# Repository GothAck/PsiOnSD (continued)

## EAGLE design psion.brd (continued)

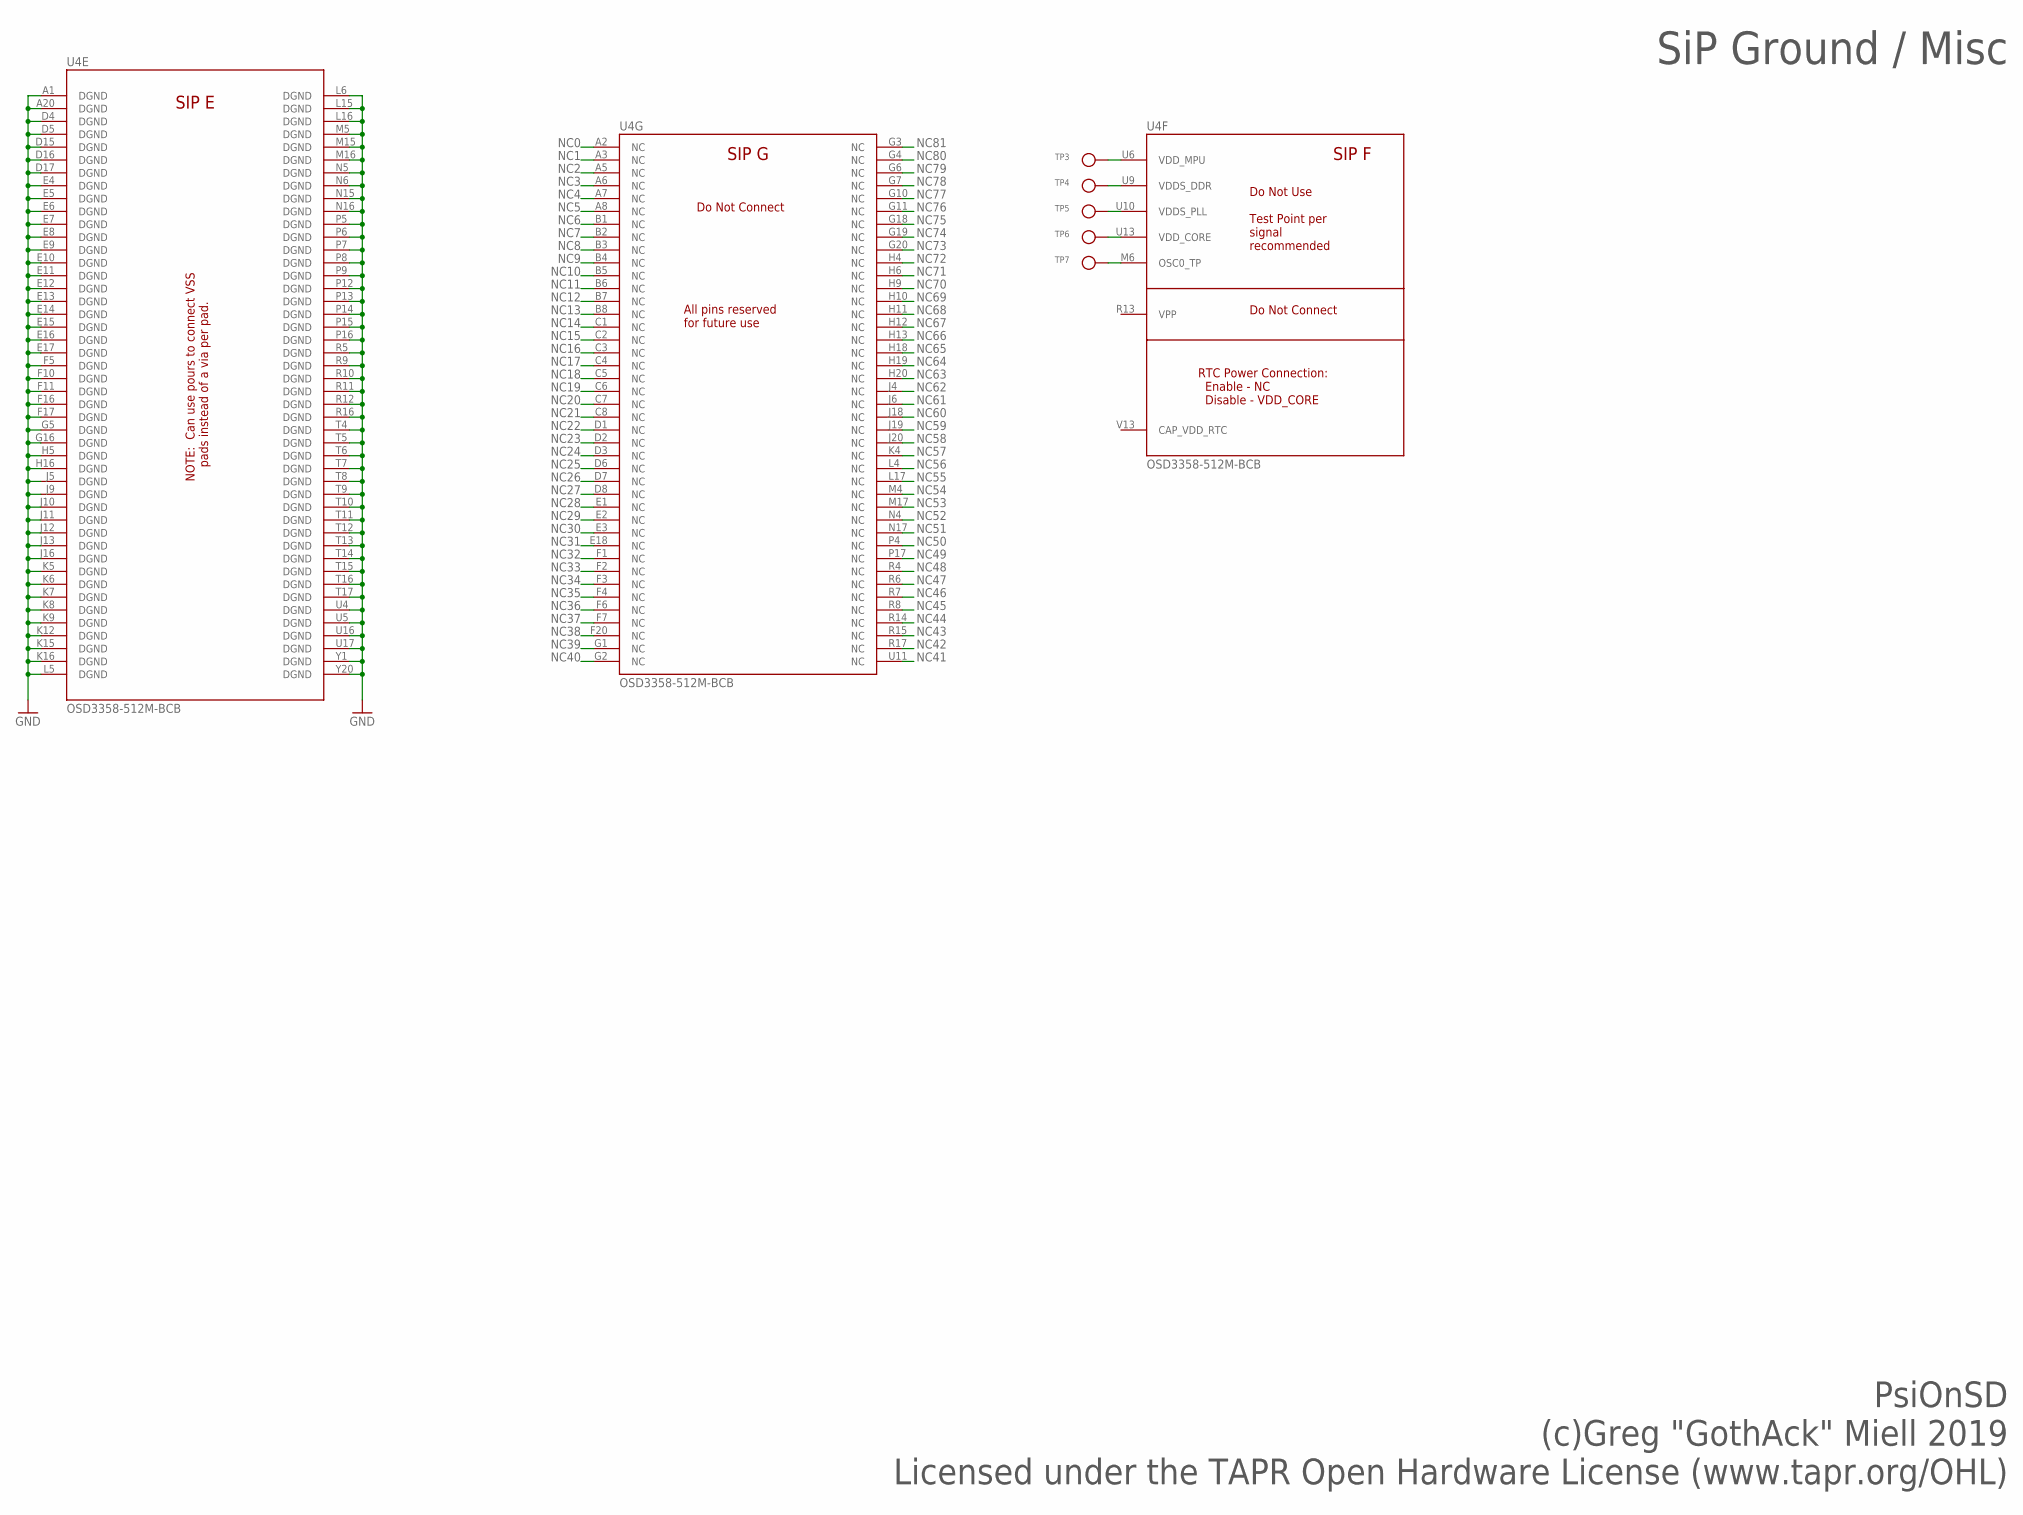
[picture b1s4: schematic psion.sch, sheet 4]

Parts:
TP3, TP4, TP5, TP6, TP7: TESTPOINTROUND1MM; TESTPOINT_ROUND_1MM
U4: OSD3358-512M-BCB; OSD335X-BGA-400

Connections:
GND: U4.A1 (DGND), U4.A20 (DGND), U4.D4 (DGND), U4.D5 (DGND), U4.D15 (DGND), U4.D16 (DGND), U4.D17 (DGND), U4.E4 (DGND), U4.E5 (DGND), U4.E6 (DGND), U4.E7 (DGND), U4.E8 (DGND), U4.E9 (DGND), U4.E10 (DGND), U4.E11 (DGND), U4.E12 (DGND), U4.E13 (DGND), U4.E14 (DGND), U4.E15 (DGND), U4.E16 (DGND), U4.E17 (DGND), U4.F5 (DGND), U4.F10 (DGND), U4.F11 (DGND), U4.F16 (DGND), U4.F17 (DGND), U4.G5 (DGND), U4.G16 (DGND), U4.H5 (DGND), U4.H16 (DGND), U4.J5 (DGND), U4.J9 (DGND), U4.J10 (DGND), U4.J11 (DGND), U4.J12 (DGND), U4.J13 (DGND), U4.J16 (DGND), U4.K5 (DGND), U4.K6 (DGND), U4.K7 (DGND), U4.K8 (DGND), U4.K9 (DGND), U4.K12 (DGND), U4.K15 (DGND), U4.K16 (DGND), U4.L5 (DGND), U4.L6 (DGND), U4.L15 (DGND), U4.L16 (DGND), U4.M5 (DGND), U4.M15 (DGND), U4.M16 (DGND), U4.N5 (DGND), U4.N6 (DGND), U4.N15 (DGND), U4.N16 (DGND), U4.P5 (DGND), U4.P6 (DGND), U4.P7 (DGND), U4.P8 (DGND), U4.P9 (DGND), U4.P12 (DGND), U4.P13 (DGND), U4.P14 (DGND), U4.P15 (DGND), U4.P16 (DGND), U4.R5 (DGND), U4.R9 (DGND), U4.R10 (DGND), U4.R11 (DGND), U4.R12 (DGND), U4.R16 (DGND), U4.T4 (DGND), U4.T5 (DGND), U4.T6 (DGND), U4.T7 (DGND), U4.T8 (DGND), U4.T9 (DGND), U4.T10 (DGND), U4.T11 (DGND), U4.T12 (DGND), U4.T13 (DGND), U4.T14 (DGND), U4.T15 (DGND), U4.T16 (DGND), U4.T17 (DGND), U4.U4 (DGND), U4.U5 (DGND), U4.U16 (DGND), U4.U17 (DGND), U4.Y1 (DGND), U4.Y20 (DGND); also elsewhere on the board
unnamed: TP3.P$1, U4.U6 (VDD_MPU)
unnamed: TP4.P$1, U4.U9 (VDDS_DDR)
unnamed: TP5.P$1, U4.U10 (VDDS_PLL)
unnamed: TP6.P$1, U4.U13 (VDD_CORE)
unnamed: TP7.P$1, U4.M6 (OSC0_TP)
NC0: U4.A2 (NC)
NC1: U4.A3 (NC)
NC2: U4.A5 (NC)
NC3: U4.A6 (NC)
NC4: U4.A7 (NC)
NC5: U4.A8 (NC)
NC6: U4.B1 (NC)
NC7: U4.B2 (NC)
NC8: U4.B3 (NC)
NC9: U4.B4 (NC)
NC10: U4.B5 (NC)
NC11: U4.B6 (NC)
NC12: U4.B7 (NC)
NC13: U4.B8 (NC)
NC14: U4.C1 (NC)
NC15: U4.C2 (NC)
NC16: U4.C3 (NC)
NC17: U4.C4 (NC)
NC18: U4.C5 (NC)
NC19: U4.C6 (NC)
NC20: U4.C7 (NC)
NC21: U4.C8 (NC)
NC22: U4.D1 (NC)
NC23: U4.D2 (NC)
NC24: U4.D3 (NC)
NC25: U4.D6 (NC)
NC26: U4.D7 (NC)
NC27: U4.D8 (NC)
NC28: U4.E1 (NC)
NC29: U4.E2 (NC)
NC30: U4.E3 (NC)
NC31: U4.E18 (NC)
NC32: U4.F1 (NC)
NC33: U4.F2 (NC)
NC34: U4.F3 (NC)
NC35: U4.F4 (NC)
NC36: U4.F6 (NC)
NC37: U4.F7 (NC)
NC38: U4.F20 (NC)
NC39: U4.G1 (NC)
NC40: U4.G2 (NC)
NC41: U4.U11 (NC)
NC42: U4.R17 (NC)
NC43: U4.R15 (NC)
NC44: U4.R14 (NC)
NC45: U4.R8 (NC)
NC46: U4.R7 (NC)
NC47: U4.R6 (NC)
NC48: U4.R4 (NC)
NC49: U4.P17 (NC)
NC50: U4.P4 (NC)
NC51: U4.N17 (NC)
NC52: U4.N4 (NC)
NC53: U4.M17 (NC)
NC54: U4.M4 (NC)
NC55: U4.L17 (NC)
NC56: U4.L4 (NC)
NC57: U4.K4 (NC)
NC58: U4.J20 (NC)
NC59: U4.J19 (NC)
NC60: U4.J18 (NC)
NC61: U4.J6 (NC)
NC62: U4.J4 (NC)
NC63: U4.H20 (NC)
NC64: U4.H19 (NC)
NC65: U4.H18 (NC)
NC66: U4.H13 (NC)
NC67: U4.H12 (NC)
NC68: U4.H11 (NC)
NC69: U4.H10 (NC)
NC70: U4.H9 (NC)
NC71: U4.H6 (NC)
NC72: U4.H4 (NC)
NC73: U4.G20 (NC)
NC74: U4.G19 (NC)
NC75: U4.G18 (NC)
NC76: U4.G11 (NC)
NC77: U4.G10 (NC)
NC78: U4.G7 (NC)
NC79: U4.G6 (NC)
NC80: U4.G4 (NC)
NC81: U4.G3 (NC)

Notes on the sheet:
PsiOnSD (c)Greg "GothAck" Miell 2019 Licensed under the TAPR Open Hardware License (www.tapr.org/OHL)
SiP Ground / Misc

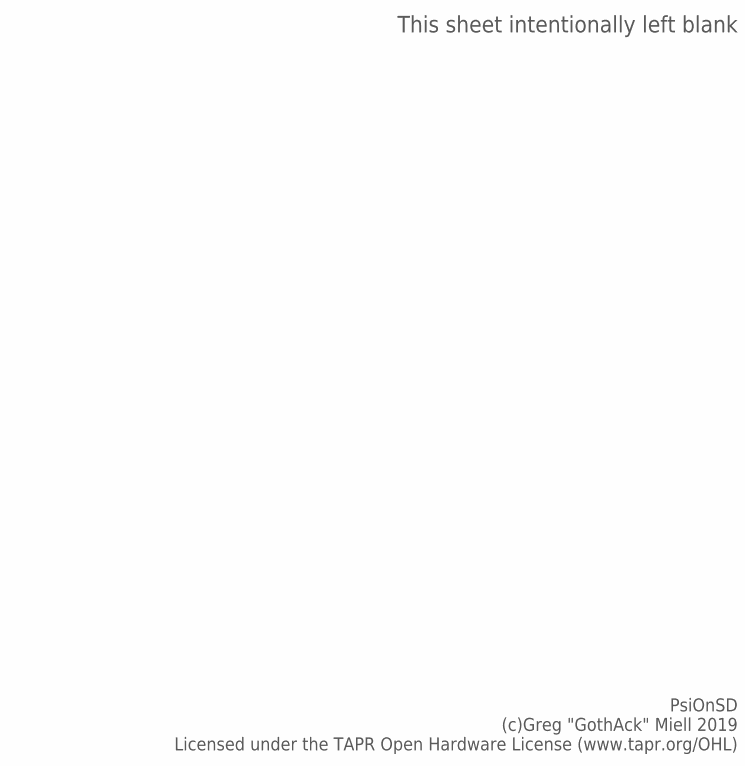
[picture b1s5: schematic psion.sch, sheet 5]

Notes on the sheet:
PsiOnSD (c)Greg "GothAck" Miell 2019 Licensed under the TAPR Open Hardware License (www.tapr.org/OHL)
This sheet intentionally left blank

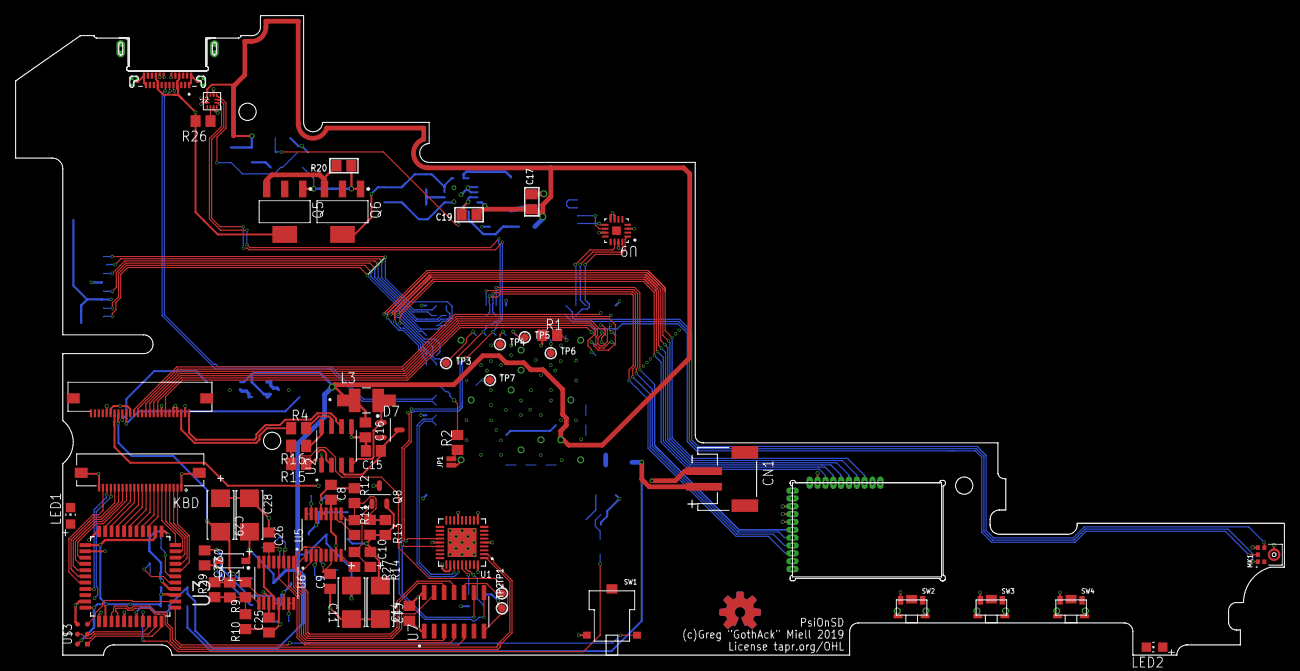
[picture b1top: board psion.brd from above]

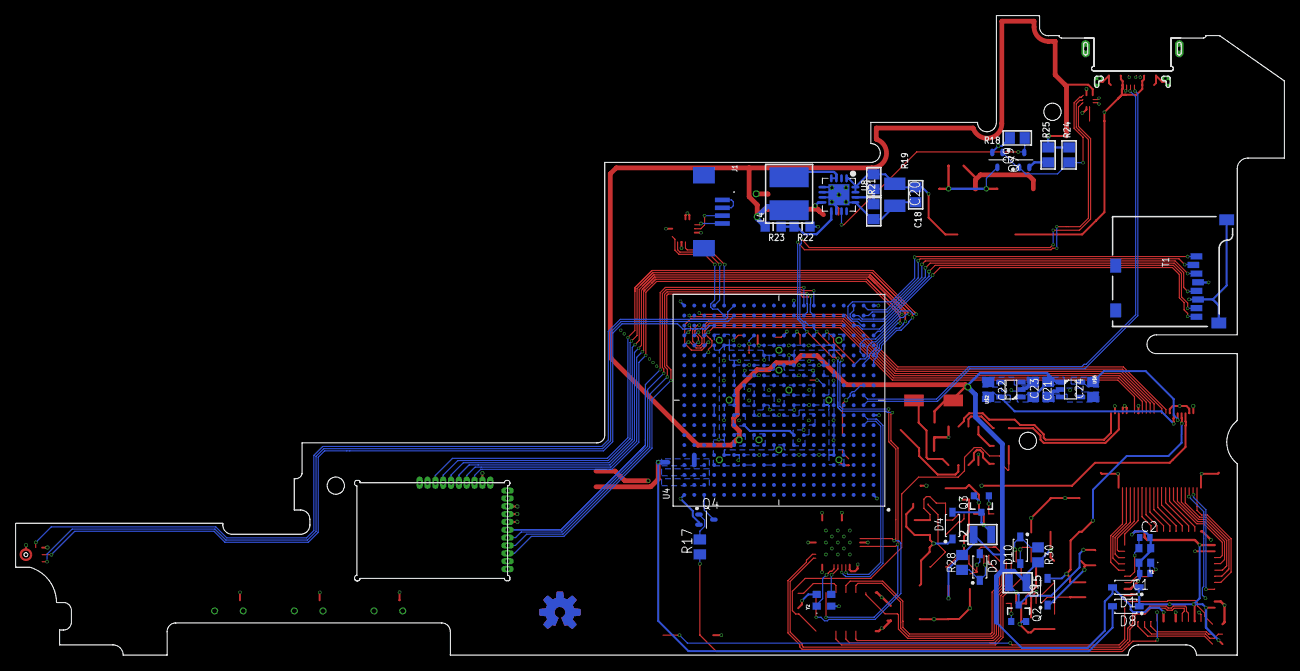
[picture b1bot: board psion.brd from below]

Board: 4 copper layers, 161.7 x 81.5 mm, 108 parts (41 on the bottom side), 145 nets.

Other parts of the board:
U$5, U$7: OSHWLOGO_TOP_0.2

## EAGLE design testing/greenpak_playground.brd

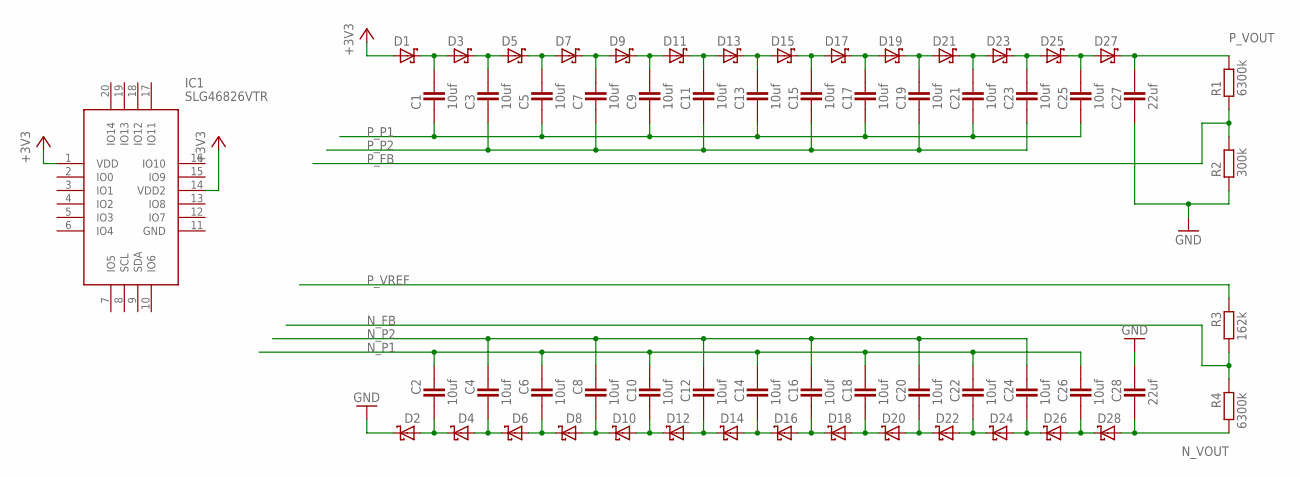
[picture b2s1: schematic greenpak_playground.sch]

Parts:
C1, C2, C3, C4, C5, C6, C7, C8, C9, C10, C11, C12, C13, C14, C15, C16, C17, C18, C19, C20, C21, C22, C23, C24, C25, C26: 10uf; CAPC3225X168N
C27, C28: 22uf; CAPC3225X168N
D1, D2, D3, D4, D5, D6, D7, D8, D9, D10, D11, D12, D13, D14, D15, D16, D17, D18, D19, D20, D21, D22, D23, D24, D25, D26, D27, D28: SCHOTTKY_SOT-23; SOT95P280X135-3N
IC1: SLG46826VTR; QFN40P200X300X60-20N
R1, R4: 6300k; RESC2012X70N
R2: 300k; RESC2012X70N
R3: 162k; RESC2012X70N

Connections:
+3V3: D1.1 (A), IC1.1 (VDD), IC1.14 (VDD2)
GND: C27.1, C28.1, D2.3 (C), IC1.11 (GND), R2.1
unnamed: C1.2, D1.3 (C), D3.1 (A)
unnamed: C3.2, D3.3 (C), D5.1 (A)
unnamed: C5.2, D5.3 (C), D7.1 (A)
unnamed: C7.2, D7.3 (C), D9.1 (A)
unnamed: C9.2, D9.3 (C), D11.1 (A)
unnamed: C11.2, D11.3 (C), D13.1 (A)
unnamed: C13.2, D13.3 (C), D15.1 (A)
unnamed: C15.2, D15.3 (C), D17.1 (A)
unnamed: C2.2, D2.1 (A), D4.3 (C)
unnamed: C4.2, D4.1 (A), D6.3 (C)
unnamed: C6.2, D6.1 (A), D8.3 (C)
unnamed: C8.2, D8.1 (A), D10.3 (C)
unnamed: C10.2, D10.1 (A), D12.3 (C)
unnamed: C12.2, D12.1 (A), D14.3 (C)
unnamed: C14.2, D14.1 (A), D16.3 (C)
unnamed: C16.2, D16.1 (A), D18.3 (C)
unnamed: C18.2, D18.1 (A), D20.3 (C)
unnamed: C26.2, D26.1 (A), D28.3 (C)
unnamed: C17.2, D17.3 (C), D19.1 (A)
unnamed: C19.2, D19.3 (C), D21.1 (A)
unnamed: C21.2, D21.3 (C), D23.1 (A)
unnamed: C23.2, D23.3 (C), D25.1 (A)
unnamed: C25.2, D25.3 (C), D27.1 (A)
unnamed: C24.2, D24.1 (A), D26.3 (C)
unnamed: C22.2, D22.1 (A), D24.3 (C)
unnamed: C20.2, D20.1 (A), D22.3 (C)
N_FB: R3.2, R4.1
N_P1: C2.1, C6.1, C10.1, C14.1, C18.1, C22.1, C26.1
N_P2: C4.1, C8.1, C12.1, C16.1, C20.1, C24.1
N_VOUT: C28.2, D28.1 (A), R4.2
P_FB: R1.1, R2.2
P_P1: C1.1, C5.1, C9.1, C13.1, C17.1, C21.1, C25.1
P_P2: C3.1, C7.1, C11.1, C15.1, C19.1, C23.1
P_VOUT: C27.2, D27.3 (C), R1.2
P_VREF: R3.1

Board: 2 copper layers, 61 parts (0 on the bottom side), 36 nets, no tracks yet.

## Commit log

2019-08-30 Added README
2019-08-31 work on lcd bias power + pdfs
2019-08-31 Finally fixed outer dimension polygon + more routing + pdf
2019-09-01 routing + gerbers + pdfs + docs
2019-09-01 add TAPR OHL license
2019-09-01 Add OSHW to brd
2019-09-04 Remove CAM outputs
2019-09-04 OSHPark CAM & ignore outputs
2019-09-04 moar datasheets
2019-09-04 Added audio compoments, massive board changes to accommodate physical space & rf restrictions
2019-09-04 Cleared some DRC issues
2019-09-04 more drc issues
